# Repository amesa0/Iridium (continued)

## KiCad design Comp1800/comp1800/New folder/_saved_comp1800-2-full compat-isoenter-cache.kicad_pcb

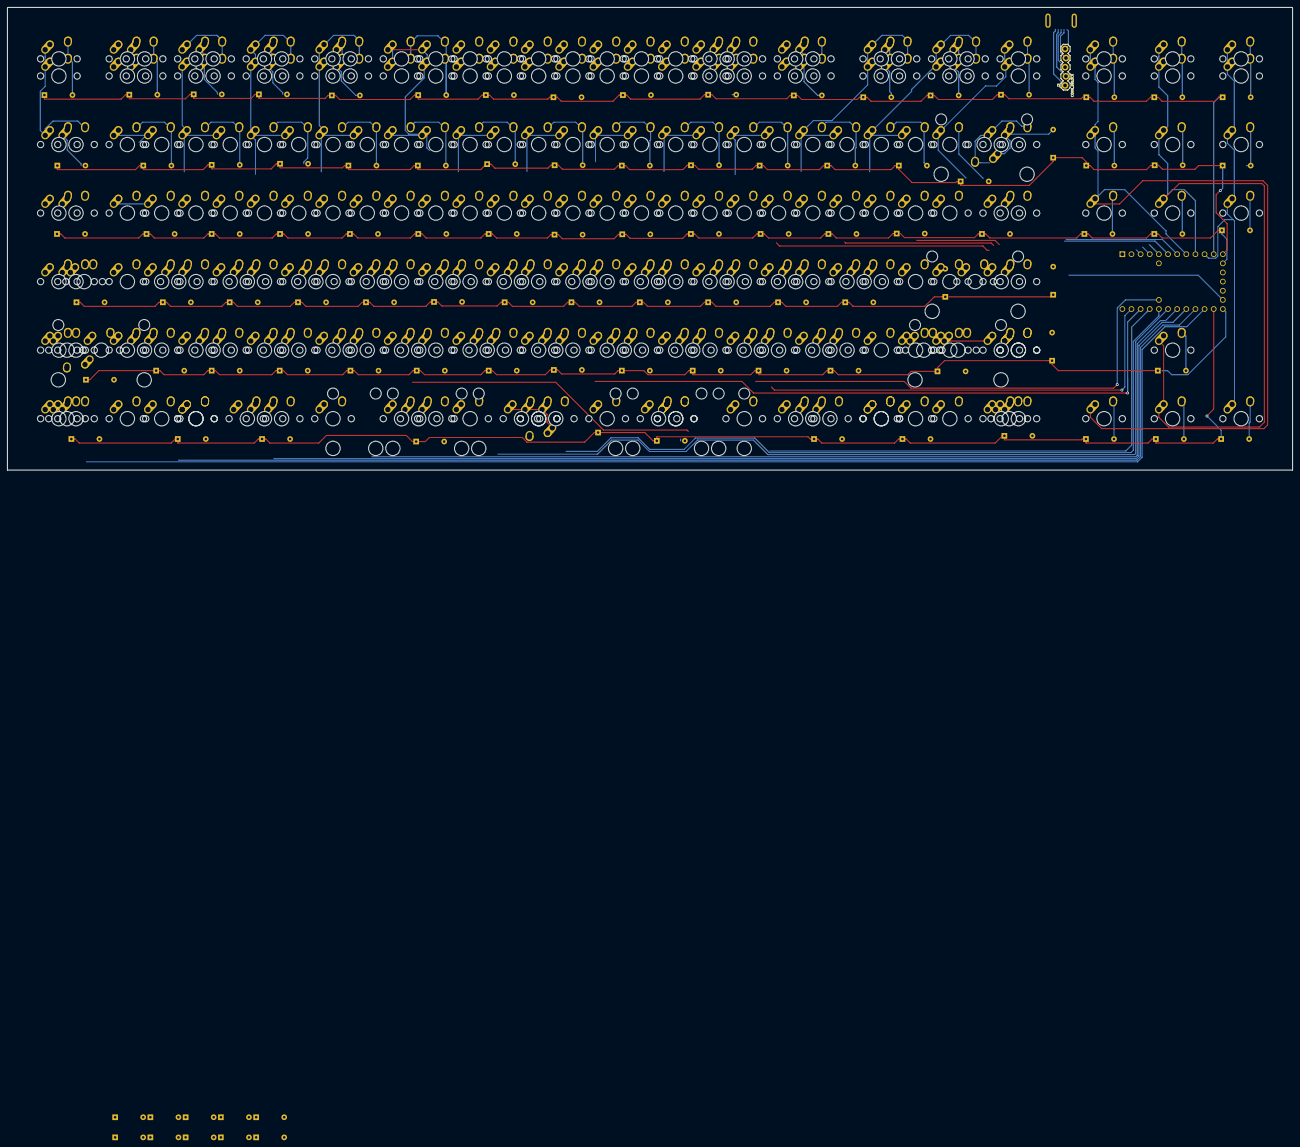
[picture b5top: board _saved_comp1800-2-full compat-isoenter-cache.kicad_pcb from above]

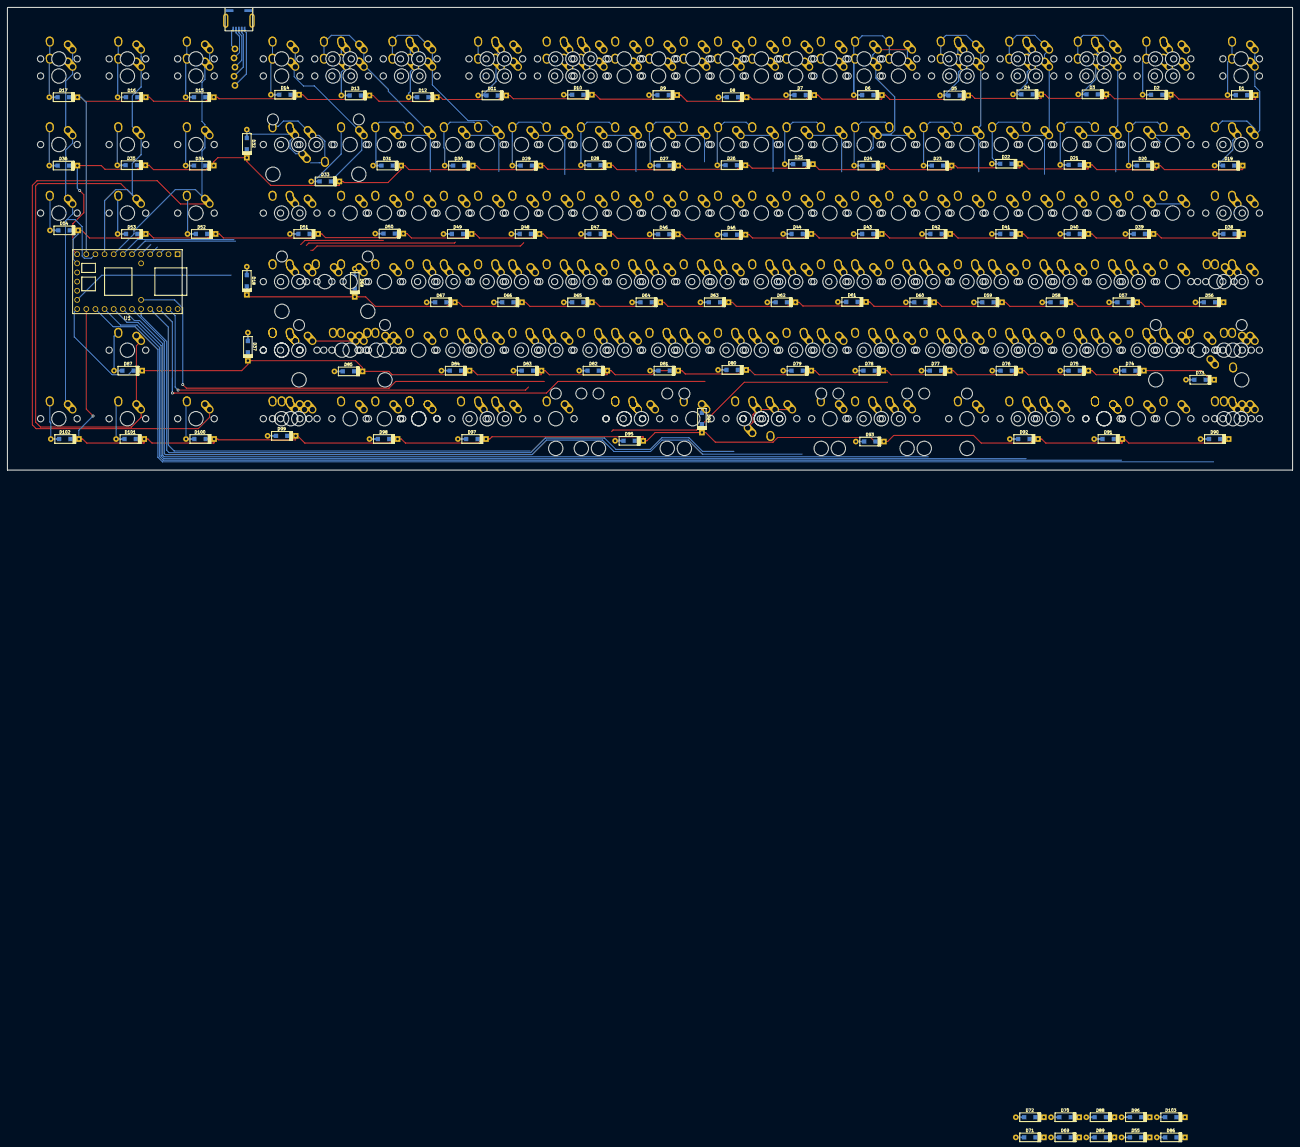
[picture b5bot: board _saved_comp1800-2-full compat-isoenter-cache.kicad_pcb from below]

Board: 2 copper layers, 357.2 x 128.6 mm, 358 parts (105 on the bottom side), 130 nets.

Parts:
;1, ;2: KEYSW; MX-1U-NoLED
D1, D2, D3, D4, D5, D6, D7, D8, D9, D10, D11, D12, D13, D14, D15, D16, D17, D18, D19, D20, D21, D22, D23, D24, D25, D26, D27, D28, D29, D30, D31, D32, D33, D34, D35, D36, D37, D38, D39, D40, D41, D42, D43, D44, D45, D46, D47, D48, D49, D50, D51, D52, D53, D54, D55, D56, D57, D58, D59, D60, D61, D62, D63, D64, D65, D66, D67, D68, D69, D70, D71, D72, D73, D74, D75, D76, D77, D78, D79, D80, D81, D82, D83, D84, D85, D86, D87, D88, D89, D90, D91, D92, D93, D94, D95, D96, D97, D98, D99, D100, D101, D102, D103: D; D_SOD123_axial
J1: USB_mini_micro_B; USB_miniB_hirose_5S8
J2: CONN_05LOCK; 1X05_LOCK
K0, K0b1, K0c1, K1, K2, K2b1, K3, K4, K5, K6, K7, K7b1, K8, K8b1, K9, K9b1, K10, K11, K12, K13, K14, K15, K16, K17, K18, K19, K20, K21, K.1, K.2, K.b1: KEYSW; MX-1U-NoLED
K'1, K'2: KEYSW; MX-1U-NoLED
K*b1: KEYSW; MX-1U-NoLED
K,1, K,2: KEYSW; MX-1U-NoLED
K-1, K-2: KEYSW; MX-1U-NoLED
K/a1, K/a2: KEYSW; MX-1U-NoLED
K/b1: KEYSW; MX-1U-NoLED
K/b2: KEYSW; MX-1.75U-NoLED
K=1, K=2: KEYSW; MX-1U-NoLED
K\1: KEYSW; MX-1.5U-NoLED
Kalta1: KEYSW; MX-1.25U-NoLED
Kaltb1: KEYSW; MX-1.5U-NoLED
Kaltc1: KEYSW; MX-1.25U-NoLED
Kaltd1: KEYSW; MX-1.5U-NoLED
Kbsa1: KEYSW; MX-1U-NoLED
Kbsa2: KEYSW; MX-1.5U-NoLED
Kbsb1: KEYSW; MX-2U-ReversedStabilizers-NoLED
Kcaps1: KEYSW; MX-1.75U-NoLED
Kcaps2: KEYSW; MX-1.5U-NoLED
Kctrla1: KEYSW; MX-1.25U-NoLED
Kctrlb1: KEYSW; MX-1.5U-NoLED
Kctrld1: KEYSW; MX-1.5U-NoLED
Kdel2: KEYSW; MX-1U-NoLED
Kenter1: KEYSW; MX-2.25U-NoLED
Kenter2: KEYSW; MX-1U-NoLED
Kenter3: KEYSW; MX-1.5U-NoLED
Kesc1, Kesc1#2, Kesc2, Kesc2#2: KEYSW; MX-1U-NoLED
Kf1a1, Kf1a1#2, Kf1b1, Kf1b1#2, Kf2a1, Kf2a1#2, Kf2b1, Kf2b1#2, Kf3a1, Kf3a1#2, Kf3b1, Kf3b1#2, Kf4a1, Kf4a1#2, Kf4b1, Kf4b1#2, Kf5a1, Kf5a1#2, Kf6a1, Kf6a1#2, Kf7a1, Kf7a1#2, Kf8a1, Kf8a1#2, Kf8b1, Kf8b1#2, Kf9a1, Kf9a1#2, Kf9b1, Kf9b1#2, Kf10a1, Kf10a1#2, Kf10b1, Kf10b1#2, Kf11a1, Kf11a1#2, Kf11b1, Kf11b1#2, Kf12a1, Kf12a1#2: KEYSW; MX-1U-NoLED
Kfn1, Kfn2: KEYSW; MX-1U-NoLED
Kfn3: KEYSW; MX-1.5U-NoLED
Kiso1u1, Kiso1u2: KEYSW; MX-1U-NoLED
Knum1: KEYSW; MX-1U-NoLED
Kortho1, Kortho1#2, Kortho6, Kortho6#2, Kortho7, Kortho7#2, Kortho8, Kortho8#2, Kortho9, Kortho9#2, Kortho10, Kortho10#2, Kortho15, Kortho16, Kortho17, Kortho18, Kortho19, Kortho20, Kortho21, Kortho22, Kortho23, Kortho24, Kortho25, Kortho26, Kortho27, Kortho28, Kortho29, Kortho30, Kortho31, Kortho32, Kortho33, Kortho34, Kortho35, Kortho36, Kortho37, Kortho38, Kortho39, Kortho40, Kortho41, Kortho42, Kortho43, Kortho44, Kortho45, Kortho46, Kortho47, Kortho48, Kortho49, Kortho50, Kortho51, Kortho52, Kortho53, Kortho54, Kortho55, Kortho56, Kortho57, Kortho58, Kortho59, Kortho60, Kortho61, Kortho62, Kortho63, Kortho64, Kortho65, Kortho66, Kortho67, Kortho68, Kortho69, Kortho70, Kortho71, Kortho72, Kortho73, Kortho74: KEYSW; MX-1U-NoLED
Kpause1, Kpause1#2: KEYSW; MX-1U-NoLED
Kprnt1, Kprnt1#2: KEYSW; MX-1U-NoLED
Kscrll1, Kscrll1#2: KEYSW; MX-1U-NoLED
Kshftb1: KEYSW; MX-2.25U-NoLED
Kshftc1: KEYSW; MX-1.25U-NoLED
Kshftc2: KEYSW; MX-1.5U-NoLED
Kshfte1: KEYSW; MX-2.75U-NoLED
Kspacea1: KEYSW; MX-2.25U-NoLED
Kspaceb1: KEYSW; MX-2.75U-NoLED
Kspaced1, Kspaced1#2: KEYSW; MX-1.25U-NoLED
Kspaceg1: KEYSW; MX-7U-ReversedStabilizers-NoLED
Kspaceh1: KEYSW; MX-2.75U-NoLED
Kspacei1: KEYSW; MX-2.25U-NoLED
Ktab1: KEYSW; MX-1.5U-NoLED
Ktilde1: KEYSW; MX-1U-NoLED
Ktilde2: KEYSW; MX-1.5U-NoLED
Kwina1: KEYSW; MX-1.25U-NoLED
Kwinb1: KEYSW; MX-1U-NoLED
Kwinc1: KEYSW; MX-1.25U-NoLED
Kwind1: KEYSW; MX-1U-NoLED
U1: TEENSY2.0; Teensy2.0
a1, a2: KEYSW; MX-1U-NoLED
b1, b2: KEYSW; MX-1U-NoLED
c1, c2: KEYSW; MX-1U-NoLED
d1, d2: KEYSW; MX-1U-NoLED
e1: KEYSW; MX-1U-NoLED
f1, f2: KEYSW; MX-1U-NoLED
g1, g2: KEYSW; MX-1U-NoLED
h1, h2: KEYSW; MX-1U-NoLED
i1: KEYSW; MX-1U-NoLED
j1, j2: KEYSW; MX-1U-NoLED
k1, k2: KEYSW; MX-1U-NoLED
kctrlc1: KEYSW; MX-1.25U-NoLED
l1, l2: KEYSW; MX-1U-NoLED
m1, m2: KEYSW; MX-1U-NoLED
n1, n2: KEYSW; MX-1U-NoLED
o1: KEYSW; MX-1U-NoLED
p1: KEYSW; MX-1U-NoLED
q1: KEYSW; MX-1U-NoLED
r1: KEYSW; MX-1U-NoLED
s1, s2: KEYSW; MX-1U-NoLED
t1: KEYSW; MX-1U-NoLED
u1: KEYSW; MX-1U-NoLED
v1, v2: KEYSW; MX-1U-NoLED
w1: KEYSW; MX-1U-NoLED
x1, x2: KEYSW; MX-1U-NoLED
y1: KEYSW; MX-1U-NoLED
z1, z2: KEYSW; MX-1U-NoLED

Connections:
unnamed: ;1.1, ;2.2, D66.2, Kortho40.2
unnamed: D1.2, Kesc1.2, Kesc1#2.2
unnamed: D2.2, Kf1a1.2, Kf1a1#2.2, Kortho1.2, Kortho1#2.2
unnamed: D3.2, Kf1b1.2, Kf1b1#2.2, Kf2a1.1, Kf2a1#2.1
unnamed: D4.2, Kf2b1.2, Kf2b1#2.2, Kf3a1.1, Kf3a1#2.1
unnamed: D5.2, Kf3b1.2, Kf3b1#2.2, Kf4a1.1, Kf4a1#2.1
unnamed: D6.2, Kf4b1.2, Kf4b1#2.2, Kf5a1.2, Kf5a1#2.2
unnamed: D7.2, Kf6a1.2, Kf6a1#2.2, Kortho6.2, Kortho6#2.2
unnamed: D8.2, Kf7a1.2, Kf7a1#2.2, Kortho7.2, Kortho7#2.2
unnamed: D9.2, Kf8a1.2, Kf8a1#2.2, Kortho8.2, Kortho8#2.2
unnamed: D10.2, Kf8b1.2, Kf8b1#2.2, Kf9a1.1, Kf9a1#2.1, Kortho9.2, Kortho9#2.2
unnamed: D11.2, Kf9b1.2, Kf9b1#2.2, Kf10a1.1, Kf10a1#2.1, Kortho10.2, Kortho10#2.2
unnamed: D12.2, Kf10b1.2, Kf10b1#2.2, Kf11a1.1, Kf11a1#2.1
unnamed: D13.2, Kf11b1.2, Kf11b1#2.2, Kf12a1.1, Kf12a1#2.1
unnamed: D14.2, Kesc2.2, Kesc2#2.2
unnamed: D15.2, Kprnt1.2, Kprnt1#2.2
unnamed: D16.2, Kscrll1.2, Kscrll1#2.2
unnamed: D17.2, Kpause1.2, Kpause1#2.2
unnamed: D18.2, Kenter1.2, Kenter3.1
unnamed: D19.2, Ktilde1.2, Ktilde2.1
unnamed: D20.2, K1.2, K10.2
unnamed: D21.2, K2.2, K13.2
unnamed: D22.2, K3.2, K14.2
unnamed: D23.2, K4.2, K15.2
unnamed: D24.2, K5.2, K16.2
unnamed: D25.2, K6.2, K17.2
unnamed: D26.2, K7.2, K18.2
unnamed: D27.2, K8.2, K19.2
unnamed: D28.2, K9.2, K20.2
unnamed: D29.2, K0.2, K21.2
unnamed: D30.2, K-1.2, K-2.2
unnamed: D31.2, K=1.2, K=2.2
unnamed: D32.2, Kbsa1.1, Kbsa2.2, Kbsb1.1
unnamed: D33.2, Kdel2.2
unnamed: D34.2, Knum1.2
unnamed: D35.2, K/b1.2
unnamed: D36.2, K*b1.2
unnamed: D37.2, Kfn1.1, Kfn3.2, Kortho58.2, Kshfte1.2
unnamed: D38.2, Kortho15.2, Ktab1.2
unnamed: D39.2, Kortho16.2, q1.2
unnamed: D40.2, Kortho17.2, w1.2
unnamed: D41.2, Kortho18.2, e1.2
unnamed: D42.2, Kortho19.2, r1.2
unnamed: D43.2, t1.2
unnamed: D44.2, y1.2
unnamed: D45.2, Kortho22.2, u1.2
unnamed: D46.2, Kortho23.2, i1.2
unnamed: D47.2, Kortho24.2, o1.2
unnamed: D48.2, Kortho25.2, p1.2
unnamed: D49.2, K11.2, Kortho26.2
unnamed: D50.2, K12.2, Kortho27.2
unnamed: D51.2, K\1.2, Kortho28.2
unnamed: D52.2, K7b1.2
unnamed: D53.2, K8b1.2
unnamed: D54.2, K9b1.2
unnamed: D56.2, Kcaps1.2, Kcaps2.2, Kortho30.2
unnamed: D57.2, Kortho31.2, a1.1, a2.2
unnamed: D58.2, Kortho32.2, s1.1, s2.2
unnamed: D59.2, Kortho33.2, d1.1, d2.2
unnamed: D60.2, Kortho34.2, f1.1, f2.2
unnamed: D61.2, Kortho35.2, g1.1, g2.2
unnamed: D62.2, Kortho36.2, h1.1, h2.2
unnamed: D63.2, Kortho37.2, j1.1, j2.2
unnamed: D64.2, Kortho38.2, k1.1, k2.2
unnamed: D65.2, Kortho39.2, l1.1, l2.2
unnamed: D67.2, K'1.1, K'2.2, Kortho41.2
unnamed: D68.2, Kenter2.2, Kortho42.2
unnamed: D69.2, Kortho29.2
unnamed: D70.2, Kortho44.2
unnamed: D71.2, Kortho59.2
unnamed: D72.2, Kortho64.2
unnamed: D73.2, Kortho45.2, Kshftb1.2, Kshftc1.2, Kshftc2.2
unnamed: D74.2, Kiso1u1.2, Kiso1u2.1, Kortho46.2
unnamed: D75.2, Kortho47.2, z1.2, z2.1
unnamed: D76.2, Kortho48.2, x1.2, x2.1
unnamed: D77.2, Kortho49.2, c1.2, c2.1
unnamed: D78.2, Kortho50.2, v1.2, v2.1
unnamed: D79.2, Kortho51.2, b1.2, b2.1
unnamed: D80.2, Kortho52.2, n1.2, n2.1
unnamed: D81.2, Kortho53.2, m1.2, m2.1
unnamed: D82.2, K,1.2, K,2.1, Kortho54.2
unnamed: D83.2, K.1.2, K.2.1, Kortho55.2
unnamed: D84.2, K/a1.2, K/a2.1, Kortho56.2
unnamed: D85.2, K/b2.2, Kfn2.2, Kortho57.2
unnamed: D86.2, Kortho66.2
unnamed: D87.2, K2b1.2
unnamed: D88.2, Kortho67.2
unnamed: D89.2, Kortho69.2
unnamed: D90.2, Kctrla1.2, Kctrlb1.2, Kortho61.2
unnamed: D91.2, Kortho62.2, Kwina1.2, Kwinb1.2
unnamed: D92.2, Kalta1.2, Kaltb1.2, Kortho63.2
unnamed: D93.2, Kortho65.2, Kspacea1.1, Kspaceb1.2
unnamed: D94.2, Kortho60.2, Kspaced1.2, Kspaced1#2.2, Kspaceg1.2
unnamed: D95.2, Kortho68.2, Kspaceh1.2, Kspacei1.1
unnamed: D96.2, Kortho70.2
unnamed: D97.2, Kctrld1.2, Kortho71.2, kctrlc1.2
unnamed: D98.2, Kortho72.2, Kwinc1.2, Kwind1.2
unnamed: D99.2, Kaltc1.2, Kaltd1.2, Kortho73.2
unnamed: D100.2, K0b1.2
unnamed: D101.2, K0c1.2
unnamed: D102.2, K.b1.2
unnamed: D103.2, Kortho74.2
unnamed: J1.1, J2.1
unnamed: J1.2, J2.2
unnamed: J1.3, J2.3
unnamed: J1.4, J2.4
unnamed: J1.5, J2.5
col1: Kcaps1.1, Kcaps2.1, Kctrla1.1, Kctrlb1.1, Kesc1.1, Kesc1#2.1, Kortho15.1, Kortho30.1, Kortho45.1, Kortho61.1, Kshftb1.1, Kshftc1.1, Kshftc2.1, Ktab1.1, Ktilde1.1, Ktilde2.2, U1.20
col2: K1.1, K10.1, Kf1a1.1, Kf1a1#2.1, Kiso1u1.1, Kiso1u2.2, Kortho1.1, Kortho1#2.1, Kortho16.1, Kortho31.1, Kortho46.1, Kortho62.1, Kwina1.1, Kwinb1.1, U1.21, a1.2, a2.1, q1.1
col3: K2.1, K13.1, Kalta1.1, Kaltb1.1, Kf1b1.1, Kf1b1#2.1, Kf2a1.2, Kf2a1#2.2, Kortho17.1, Kortho32.1, Kortho47.1, Kortho63.1, U1.22, s1.2, s2.1, w1.1, z1.1, z2.2
col4: K3.1, K14.1, Kf2b1.1, Kf2b1#2.1, Kf3a1.2, Kf3a1#2.2, Kortho18.1, Kortho33.1, Kortho48.1, Kortho64.1, U1.23, d1.2, d2.1, e1.1, x1.1, x2.2
col5: K4.1, K15.1, Kf3b1.1, Kf3b1#2.1, Kf4a1.2, Kf4a1#2.2, Kortho19.1, Kortho34.1, Kortho49.1, Kortho65.1, Kspacea1.2, Kspaceb1.1, U1.24, c1.1, c2.2, f1.2, f2.1, r1.1
col6: K5.1, K16.1, Kf4b1.1, Kf4b1#2.1, Kf5a1.1, Kf5a1#2.1, Kortho20.1, Kortho35.1, Kortho50.1, Kortho66.1, U1.26, g1.2, g2.1, t1.1, v1.1, v2.2
col7: K6.1, K17.1, Kf6a1.1, Kf6a1#2.1, Kortho6.1, Kortho6#2.1, Kortho21.1, Kortho36.1, Kortho51.1, Kortho60.1, Kspaced1.1, Kspaced1#2.1, Kspaceg1.1, U1.25, b1.1, b2.2, h1.2, h2.1, y1.1
col8: K7.1, K18.1, Kf7a1.1, Kf7a1#2.1, Kortho7.1, Kortho7#2.1, Kortho22.1, Kortho37.1, Kortho52.1, Kortho67.1, U1.27, j1.2, j2.1, n1.1, n2.2, u1.1
col9: K8.1, K19.1, Kf8a1.1, Kf8a1#2.1, Kortho8.1, Kortho8#2.1, Kortho23.1, Kortho38.1, Kortho53.1, Kortho68.1, Kspaceh1.1, Kspacei1.2, U1.28, i1.1, k1.2, k2.1, m1.1, m2.2
col10: K9.1, K20.1, K,1.1, K,2.2, Kf8b1.1, Kf8b1#2.1, Kf9a1.2, Kf9a1#2.2, Kortho9.1, Kortho9#2.1, Kortho24.1, Kortho39.1, Kortho54.1, Kortho69.1, U1.31, l1.2, l2.1, o1.1
col11: ;1.2, ;2.1, K0.1, K21.1, K.1.1, K.2.2, Kf9b1.1, Kf9b1#2.1, Kf10a1.2, Kf10a1#2.2, Kortho10.1, Kortho10#2.1, Kortho25.1, Kortho40.1, Kortho55.1, Kortho70.1, U1.3, p1.1
col12: K11.1, K'1.2, K'2.1, K-1.1, K-2.1, K/a1.1, K/a2.2, Kctrld1.1, Kf10b1.1, Kf10b1#2.1, Kf11a1.2, Kf11a1#2.2, Kortho26.1, Kortho41.1, Kortho56.1, Kortho71.1, U1.4, kctrlc1.1
col13: K12.1, K/b2.1, K=1.1, K=2.1, Kenter2.1, Kf11b1.1, Kf11b1#2.1, Kf12a1.2, Kf12a1#2.2, Kfn2.1, Kortho27.1, Kortho42.1, Kortho57.1, Kortho72.1, Kwinc1.1, Kwind1.1, U1.5
col14: K\1.1, Kaltc1.1, Kaltd1.1, Kdel2.1, Kenter1.1, Kenter3.2, Kesc2.1, Kesc2#2.1, Kfn1.2, Kfn3.1, Kortho28.1, Kortho43.1, Kortho58.1, Kortho73.1, Kshfte1.1, U1.6
col15: D18.1, D56.1, D57.1, D58.1, D59.1, D60.1, D61.1, D62.1, D63.1, D64.1, D65.1, D66.1, D67.1, D68.1, D70.1, Kbsa1.2, Kbsa2.1, Kbsb1.2, Kortho29.1, Kortho44.1, Kortho59.1, Kortho74.1, U1.7, U1.17
col16: K0b1.1, K7b1.1, Knum1.1, Kprnt1.1, Kprnt1#2.1, U1.8
col17: K0c1.1, K2b1.1, K8b1.1, K/b1.1, Kscrll1.1, Kscrll1#2.1, U1.9
col18: K9b1.1, K*b1.1, K.b1.1, Kpause1.1, Kpause1#2.1, U1.10
row1: D1.1, D2.1, D3.1, D4.1, D5.1, D6.1, D7.1, D8.1, D9.1, D10.1, D11.1, D12.1, D13.1, D14.1, D15.1, D16.1, D17.1, D55.1, U1.11
row2: D19.1, D20.1, D21.1, D22.1, D23.1, D24.1, D25.1, D26.1, D27.1, D28.1, D29.1, D30.1, D31.1, D32.1, D33.1, D34.1, D35.1, D36.1, U1.12
row3: D38.1, D39.1, D40.1, D41.1, D42.1, D43.1, D44.1, D45.1, D46.1, D47.1, D48.1, D49.1, D50.1, D51.1, D52.1, D53.1, D54.1, D69.1, U1.13
row5: D37.1, D71.1, D73.1, D74.1, D75.1, D76.1, D77.1, D78.1, D79.1, D80.1, D81.1, D82.1, D83.1, D84.1, D85.1, D87.1, U1.18
row6: D72.1, D86.1, D88.1, D89.1, D90.1, D91.1, D92.1, D93.1, D94.1, D95.1, D96.1, D97.1, D98.1, D99.1, D100.1, D101.1, D102.1, D103.1, U1.19

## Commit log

2018-05-21 init commit
2018-05-21 Moving files
2018-05-21 shuffling
2018-05-22 65plus revision 4 in progress, TODO Routing
2018-05-22 continue working on routing added a second 2u bs compat
2018-05-22 Create LICENSE
2018-05-26 90 plus almost complete
2018-05-26 90 plus complete TODO Cosmetics, R2 routing
2018-05-26 add 90plus images
2018-05-26 images
2018-06-01 100 plus init
2018-06-01 100plus image
2018-06-01 navigation
2018-06-04 100plus-2 is working
2018-06-06 nix 100plus 1 and 2 commits corrected usb
2018-06-09 100 plus second revision
2018-06-10 100plus layout changes
2018-06-28 100plus rev3 in prog
2018-07-06 mostly 100plus corrections
2018-11-04 fake alice
2018-11-13 falice
2018-11-13 alice
